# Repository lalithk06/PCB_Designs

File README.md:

# 🖥️ PCB Designs Repository

Welcome to the **PCB Designs** repository!  
This repo contains various **KiCad PCB design projects** for electronics and embedded systems, aimed at learning and experimentation.

---

| 🔗 Project Name         | 📜 Description                                                   | ✅ Status                | 📁 Link |
|:-----------------------:|:---------------------------------------------------------------:|:------------------------|:-------:|
| 🔥 Fire Alarm System    | A light-based fire alarm circuit using an LDR and transistor.   | [x] Schematic <br> [x] PCB | [View Project](./Fire_Alarm/README.md) |
| ⚡ Relay Driver Circuit  | A single-channel relay driver for MCU load control.            | [x] Schematic <br> [x] PCB | [View Project](./Relay_Driver/README.md) |
| 🤖 PID Line Follower PCB | ESP32-based autonomous line follower with custom PCB (power zoning, motor driver, sensors). | [x] Schematic <br> [x] PCB | [View Project](https://github.com/lalithk06/PID-Line-Follower) |
| ⚡ ESP32 Smart Plug | ESP32-S3 based smart plug with mains power control, relay switching, protection, and USB interface. | [x] Schematic <br> [x] PCB | [View Project](https://github.com/lalithk06/ESP32_Smart_Plug) |
| 🌍 ESP32 Indoor Environment Quality Monitor | A 4-layer ESP32-based embedded monitoring system designed for real-time indoor environmental sensing, featuring multi-sensor I2C integration, clean power architecture, OLED interface, data logging, and battery/USB-powered operation. | [x] Schematic <br> [x] PCB | [View Project](./ESP32_IEQ_Monitor) |
| 🔌 USB-C PD Power Supply | A USB Type-C Power Delivery trigger board based on the CH224A, supporting selectable 5V/9V/12V/20V/28V outputs via DIP switches or I²C, with onboard buck conversion, input protection, voltage indication, and screw terminal output. | [x] Schematic <br> [] PCB | [View Project](./USB-C_Power_Supply) |

---

## 🛠 Tools & Workflow
- **KiCad v9.x**   → Schematic & PCB design  
- **Git & GitHub** → Version control and collaboration  
- **Markdown**     → Project documentation

---

## 🚀 How to Use
Clone the repository:
   ```bash
   git clone https://github.com/<your-username>/PCB_Designs.git

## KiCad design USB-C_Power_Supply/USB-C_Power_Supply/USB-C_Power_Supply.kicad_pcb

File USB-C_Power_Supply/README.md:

# USB-C Power Supply (5V / 9V / 12V / 20V / 28V)

A compact USB Type-C Power Delivery (USB-PD) trigger board capable of requesting fixed PDO voltages from a USB-C PD charger and providing a regulated **3.3V rail** for onboard logic. The board is based on the **CH224A USB PD Sink Controller** and supports both **DIP-switch voltage selection** and **I²C control**.

---

## Features

- USB Type-C Power Delivery Sink
- Selectable Output Voltages
  - 5V
  - 9V
  - 12V
  - 20V
  - 28V (USB PD 3.1 EPR)
- CH224A USB PD Sink Controller
- MCP16331 Buck Converter (5V–28V → 3.3V)
- TVS Surge Protection
- PMOS Reverse Polarity Protection
- USB Data Line ESD Protection
- Output Voltage Indicator LEDs
- Power Good / Error Indicator
- I²C Interface
- Screw Terminal Output
- Mounting Holes

---

# Board Overview

---

# Project Images

## Schematic

---

## PCB Layout

### Top Layer

### Bottom Layer

---

## 3D Model

### Top View

### Bottom View

---

# Hardware Architecture

## USB-C Input

The board receives power from a USB Type-C PD compliant charger.

### Components

- USB Type-C Receptacle
- TVS Protection
- PMOS Reverse Polarity Protection
- USBLC6 ESD Protection
- CH224A PD Controller

The USB connector provides:

- VBUS
- CC1
- CC2
- D+
- D-

---

## USB Power Delivery Controller

The CH224A negotiates the requested voltage with the USB PD source.

Unlike traditional USB-C sink implementations, **no external 5.1kΩ Rd resistors are required** because the CH224A integrates the complete USB sink detection circuitry internally.

---

# Voltage Selection

The requested PDO is selected using the CFG pins.

## DIP Switch Mode

Three DIP switches control:

- CFG1
- CFG2
- CFG3

| Output Voltage | CFG1 | CFG2 | CFG3 |
|---------------|------|------|------|
| 5V | X | X | X |
| 9V | 0 | 0 | 0 |
| 12V | 0 | 0 | 1 |
| 20V | 0 | 1 | 1 |
| 28V | 0 | 1 | 0 |

Where

- X = Don't Care
- 0 = GND
- 1 = Pull-up

---

# I²C Mode

The CH224A also supports I²C control.

The I²C connector exposes:

- SDA
- SCL
- GND

This allows an external MCU to dynamically request different PDO voltages without changing the DIP switches.

---

# Output

The negotiated USB PD voltage is available at:

- Screw Terminal Connector

Supported outputs

- 5V
- 9V
- 12V
- 20V
- 28V

> **Output current depends entirely on the connected USB PD adapter and USB-C cable.**

---

# 3.3V Power Supply

The onboard electronics operate from a dedicated 3.3V rail.

Power conversion:

```
    5V–28V
      │
      ▼
   MCP16331
Buck Converter
      │
      ▼
  3.3V Rail
```

The buck converter powers:

- CH224A
- MC14051
- Indicator LEDs
- I²C Interface

---

# Output Voltage Indicators

Five LEDs indicate the negotiated USB PD voltage.

| LED | Voltage |
|------|---------|
| LED1 | 5V |
| LED2 | 9V |
| LED3 | 12V |
| LED4 | 20V |
| LED5 | 28V |

Only one LED is illuminated at a time.

---

# Error Indicator

The CH224A provides a **Power Good (PG)** output.

The PG output is **Active Low**.

## Normal Operation

```
PG = LOW
```

The NMOS remains OFF.

The Error LED remains OFF.

---

## Error Condition

```
PG = HIGH
```

The NMOS turns ON.

The Error LED turns ON.

Possible causes include:

- USB PD negotiation failure
- Unsupported PDO request
- Charger removed
- Fault condition

---

# Protection Features

## TVS Protection

A TVS diode protects the VBUS line against:

- ESD
- Cable transients
- Voltage spikes

The TVS is placed immediately after the USB-C connector.

---

## Reverse Polarity Protection

A PMOS transistor provides reverse polarity protection.

Advantages

- Very low voltage drop
- Automatic recovery
- No fuse replacement required

---

## CC Line Protection

22Ω series resistors improve robustness against:

- ESD
- Ringing
- Cable transients

---

# eMarker Simulation Mode

USB PD 3.1 requires an electronically marked cable for voltages greater than 20V or powers exceeding 60W.

The CH224A provides an **eMarker Simulation Mode**.

To enable:

Connect

```
1kΩ

CC2 → GND
```

This allows requesting

- 28V PDO

using a standard USB-C connector.

Refer to the CH224A datasheet for further details.

---

# Applications

- USB PD Bench Supply
- Embedded Development
- Rapid Prototyping
- Battery Charging
- Robotics
- Industrial Electronics
- Portable Instruments
- USB PD Testing
- IoT Projects

---

# Operating Procedure

## DIP Switch Mode

1. Connect a USB PD charger.
2. Configure the DIP switches for the desired voltage.
3. Apply power.
4. The CH224A negotiates the selected PDO.
5. Verify the output voltage using the indicator LED.
6. Use the output at J2.

---

## I²C Mode

1. Connect an external MCU.
2. Initialize the CH224A over I²C.
3. Send the desired PDO request.
4. Wait for negotiation to complete.
5. Monitor the PG signal.
6. Use the negotiated output voltage.

---

# Notes

- The output voltage is available only when connected to a USB PD compliant source.
- 28V operation requires a USB PD 3.1 EPR compatible adapter.
- Maximum available current depends on the USB PD source and cable capability.
- Use high-quality USB-C cables for high-power operation.
- The board does not generate voltages internally; it only negotiates and passes through supported USB PD voltages.

---

# Specifications

| Parameter | Value |
|-----------|-------|
| Input Connector | USB Type-C |
| USB PD Version | USB PD 3.1 |
| Supported PDOs | 5V, 9V, 12V, 20V, 28V |
| Controller | CH224A |
| Logic Supply | 3.3V |
| Buck Converter | MCP16331 |
| Voltage Selection | DIP Switch / I²C |
| Output Connector | Screw Terminal |
| Reverse Polarity Protection | PMOS |
| Surge Protection | TVS |
| USB ESD Protection | USBLC6 |
| Mounting | 4 × Mounting Holes |

---

# License

This hardware design is released under the MIT License unless stated otherwise.

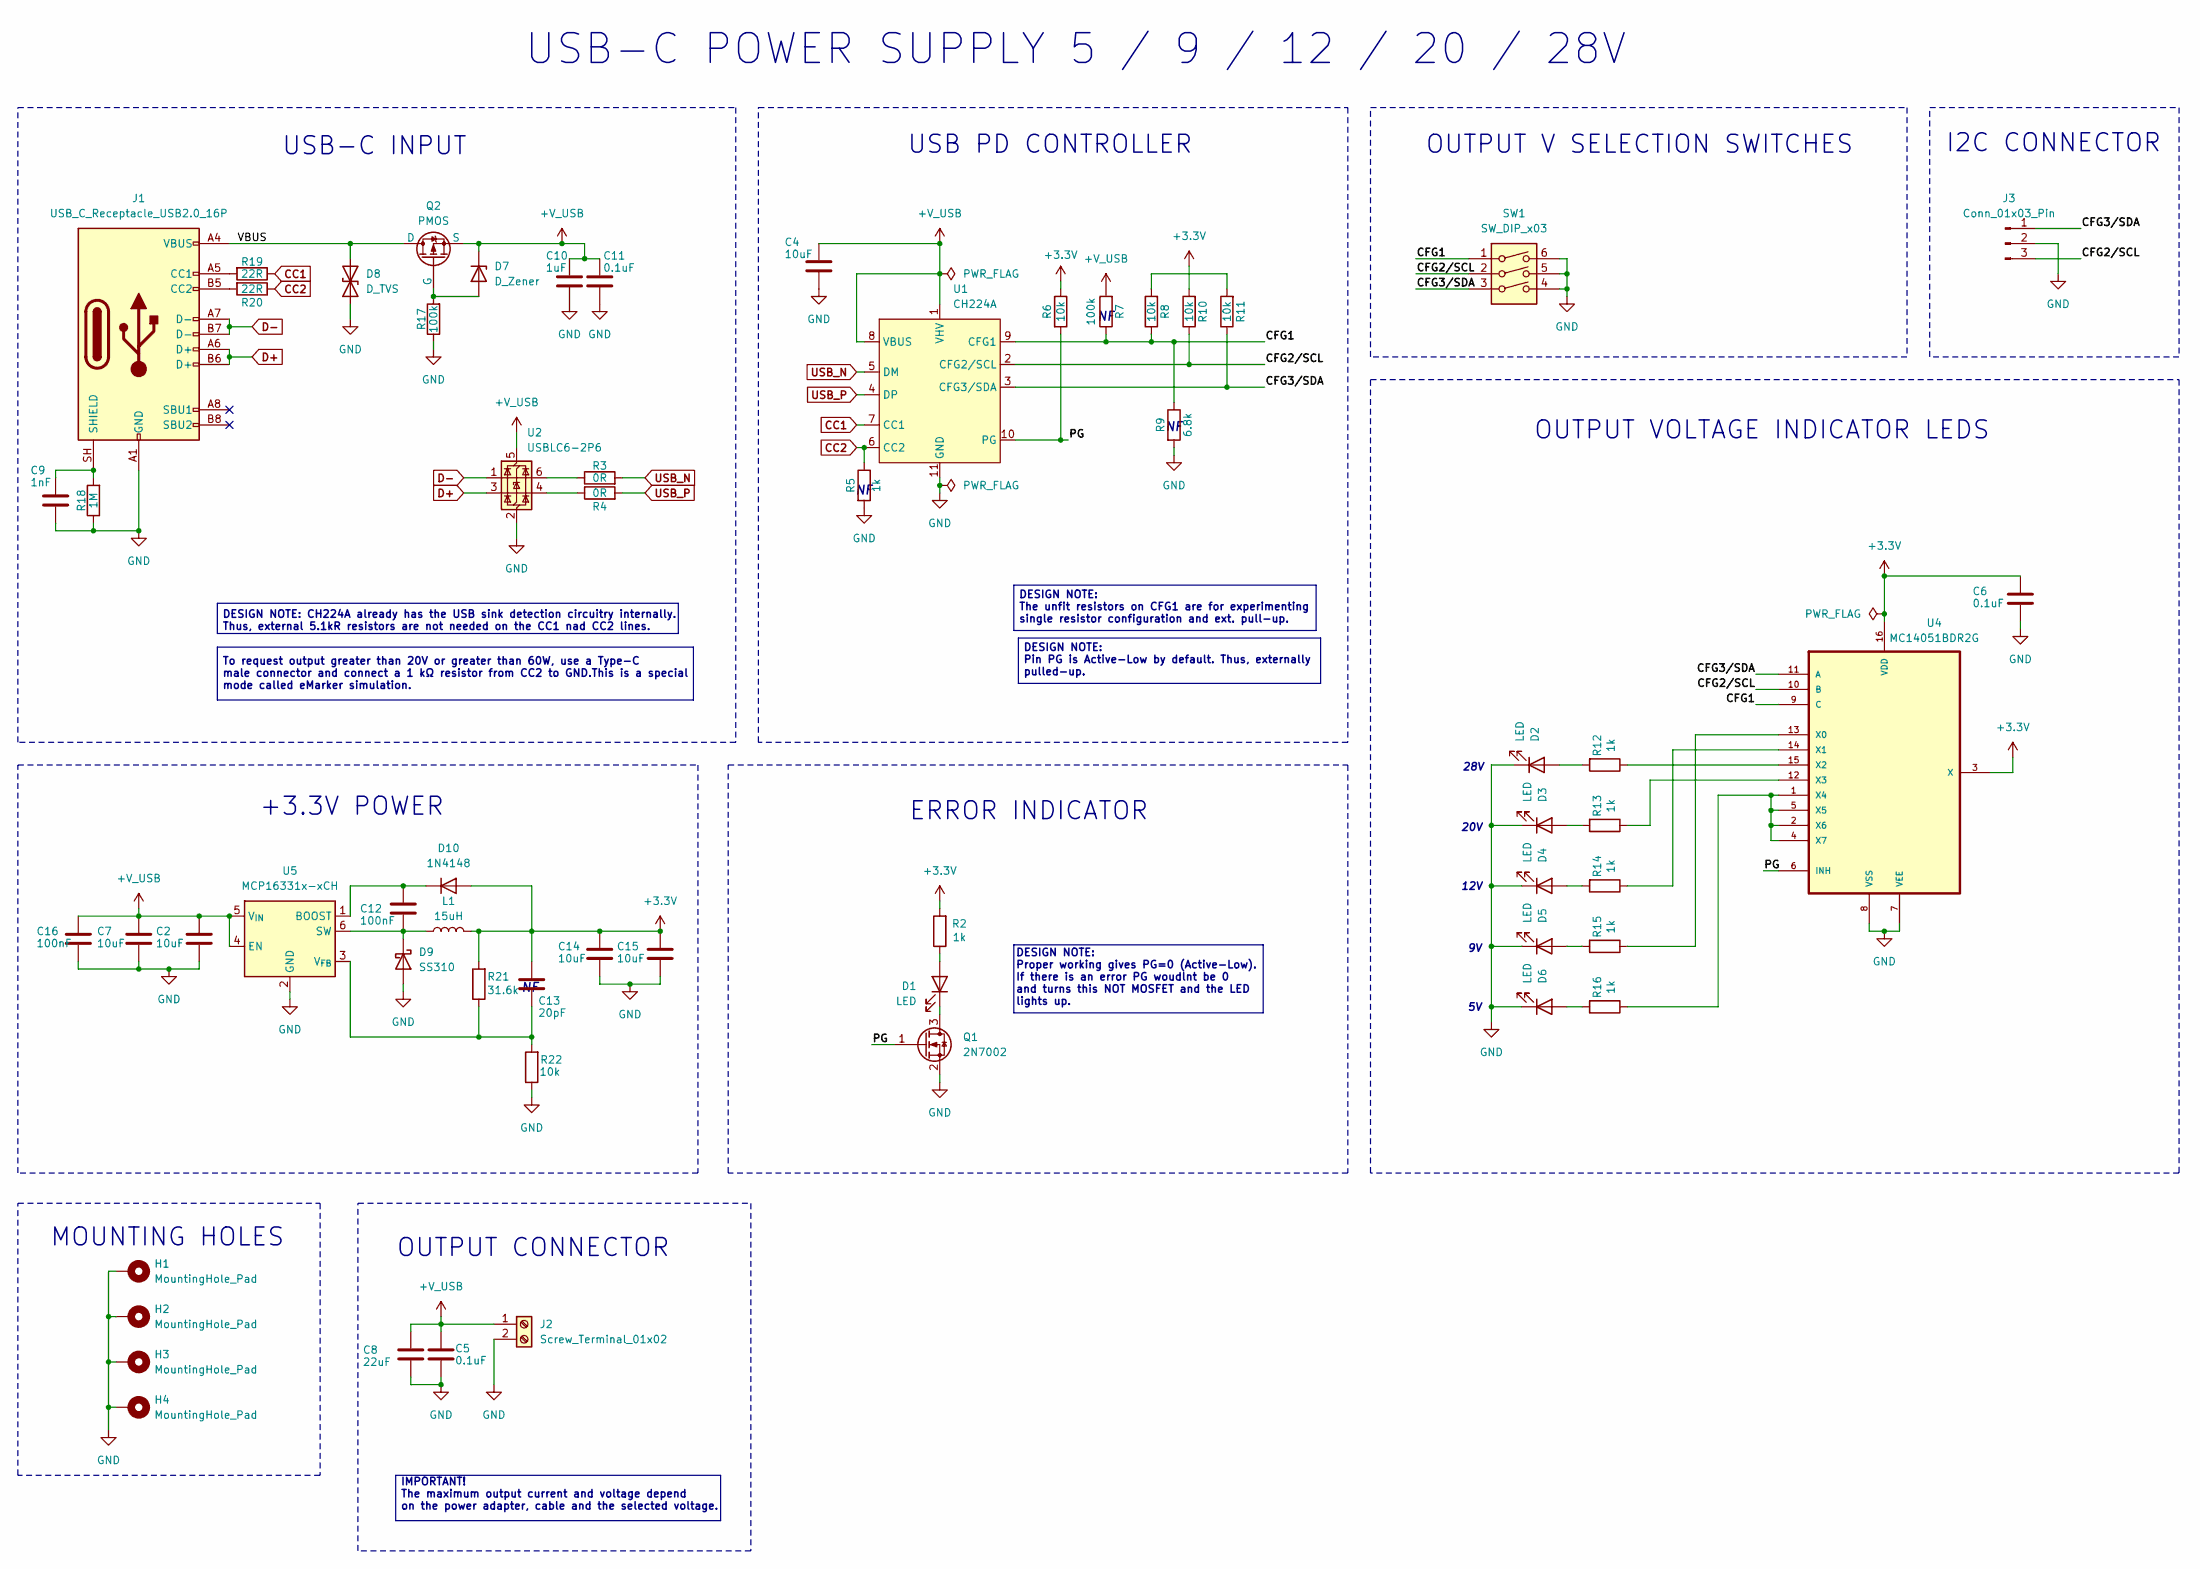
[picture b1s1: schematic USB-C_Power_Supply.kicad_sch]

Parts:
C2, C4, C7, C14, C15: 10uF; C_1206_3216Metric
C5, C6, C11: 0.1uF; C_0603_1608Metric
C8: 22uF; C_1210_3225Metric
C9: 1nF; C_0603_1608Metric
C10: 1uF; C_0805_2012Metric
C12, C16: 100nF; C_0603_1608Metric
C13: 20pF; C_0603_1608Metric
D1, D2, D3, D4, D5, D6: LED; LED_0603_1608Metric
D7: D_Zener; D_SOD-123
D8: D_TVS; D_SMB
D9: SS310; D_SMA
D10: 1N4148; D_DO-35_SOD27_P7.62mm_Horizontal
H1, H2, H3, H4: MountingHole_Pad; MountingHole_2.5mm_Pad
J1: USB_C_Receptacle_USB2.0_16P; USB_C_Receptacle_GCT_USB4105-xx-A_16P_TopMnt_Horizontal
J2: Screw_Terminal_01x02; CUI_TB007-508-02BE
J3: Conn_01x03_Pin; PinHeader_1x03_P2.54mm_Vertical
L1: 15uH; L_6.3x6.3_H3
Q1: 2N7002; SOT-23
Q2: PMOS; SOT-23
R2, R5, R12, R13, R14, R15, R16: 1k; R_0603_1608Metric
R3, R4: 0R; R_0603_1608Metric
R6, R8, R10, R11, R22: 10k; R_0603_1608Metric
R7, R17: 100k; R_0603_1608Metric
R9: 6.8k; R_0603_1608Metric
R18: 1M; R_0603_1608Metric
R19, R20: 22R; R_0603_1608Metric
R21: 31.6k; R_0603_1608Metric
SW1: SW_DIP_x03; SW_DIP_SPSTx03_Slide_6.7x9.18mm_W8.61mm_P2.54mm_LowProfile
U1: CH224A
U2: USBLC6-2P6; SOT-666
U4: MC14051BDR2G
U5: MCP16331x-xCH; SOT-23-6

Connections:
+3.3V: C6.1, C13.1, C14.1, C15.1, D10.2 (A), L1.2, R2.2, R6.1, R10.2, R21.2, U4.3 (X), U4.16 (VDD)
+V_USB: C2.1, C4.1, C5.1, C7.1, C8.1, C10.1, C11.1, C16.1, D7.1 (K), J2.1, Q2.3 (S), R7.2, U1.1 (VHV), U1.8 (VBUS), U2.5 (VBUS), U5.4 (EN), U5.5 (V_{IN})
/CFG1: R7.1, R8.1, R9.1, SW1.1, U1.9 (CFG1), U4.9 (C)
/CFG2/SCL: J3.3, R10.1, SW1.2, U1.2 (CFG2/SCL), U4.10 (B)
/CFG3/SDA: J3.1, R11.1, SW1.3, U1.3 (CFG3/SDA), U4.11 (A)
/PG: Q1.1 (G), R6.2, U1.10 (PG), U4.6 (INH)
CC1: R19.1, U1.7 (CC1)
CC2: R5.1, R20.1, U1.6 (CC2)
D+: J1.A6 (D+), J1.B6 (D+), U2.3 (I/O2)
D-: J1.A7 (D-), J1.B7 (D-), U2.1 (I/O1)
GND: C2.2, C4.2, C5.2, C6.2, C7.2, C8.2, C9.2, C10.2, C11.2, C14.2, C15.2, C16.2, D2.1 (K), D3.1 (K), D4.1 (K), D5.1 (K), D6.1 (K), D8.1 (A1), D9.2 (A), H1.1 (1_1), H2.1 (1_1), H3.1 (1_1), H4.1 (1_1), J1.A1 (GND), J1.A12 (GND), J1.B1 (GND), J1.B12 (GND), J2.2, J3.2, Q1.2 (S), R5.2, R9.2, R17.1, R18.1, R22.1, SW1.4, SW1.5, SW1.6, U1.11 (GND), U2.2 (GND), U4.7 (VEE), U4.8 (VSS), U5.2 (GND)
unnamed: D1.2 (A), R2.1
unnamed: D1.1 (K), Q1.3 (D)
unnamed: D2.2 (A), R12.2
unnamed: D3.2 (A), R13.2
unnamed: D4.2 (A), R14.2
unnamed: D5.2 (A), R15.2
unnamed: D6.2 (A), R16.2
unnamed: D7.2 (A), Q2.2 (G), R17.2
unnamed: D8.2 (A2), J1.A4 (VBUS), J1.A9 (VBUS), J1.B4 (VBUS), J1.B9 (VBUS), Q2.1 (D)
unnamed: C12.2, D9.1 (K), L1.1, U5.6 (SW)
unnamed: C12.1, D10.1 (K), U5.1 (BOOST)
unnamed: J1.A5 (CC1), R19.2
unnamed: J1.B5 (CC2), R20.2
unnamed: C9.1, J1.SH (SHIELD), R18.2
unnamed: R3.1, U2.6 (I/O1)
unnamed: R4.1, U2.4 (I/O2)
unnamed: R8.2, R11.2
unnamed: R15.1, U4.13 (X0)
unnamed: R14.1, U4.14 (X1)
unnamed: R12.1, U4.15 (X2)
unnamed: R13.1, U4.12 (X3)
unnamed: R16.1, U4.1 (X4), U4.2 (X6), U4.4 (X7), U4.5 (X5)
unnamed: C13.2, R21.1, R22.2, U5.3 (V_{FB})
USB_N: R3.2, U1.5 (DM)
USB_P: R4.2, U1.4 (DP)

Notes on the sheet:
ERROR INDICATOR
OUTPUT V SELECTION SWITCHES
DESIGN NOTE: The unfit resistors on CFG1 are for experimenting single resistor configuration and ext. pull-up.
DESIGN NOTE: Pin PG is Active-Low by default. Thus, externally pulled-up.
+3.3V POWER
USB-C INPUT
USB PD CONTROLLER
I2C CONNECTOR
DESIGN NOTE: Proper working gives PG=0 (Active-Low). If there is an error PG woudlnt be 0 and turns this NOT MOSFET and the LED lights up.
DESIGN NOTE: CH224A already has the USB sink detection circuitry internally. Thus, external 5.1kR resistors are not needed on the CC1 nad CC2 lines.
OUTPUT VOLTAGE INDICATOR LEDS
20V
OUTPUT CONNECTOR
IMPORTANT! The maximum output current and voltage depend on the power adapter, cable and the selected voltage.
To request output greater than 20V or greater than 60W, use a Type-C male connector and connect a 1 kΩ resistor from CC2 to GND.This is a special mode called eMarker simulation.
28V
MOUNTING HOLES
USB-C POWER SUPPLY 5 / 9 / 12 / 20 / 28V
12V

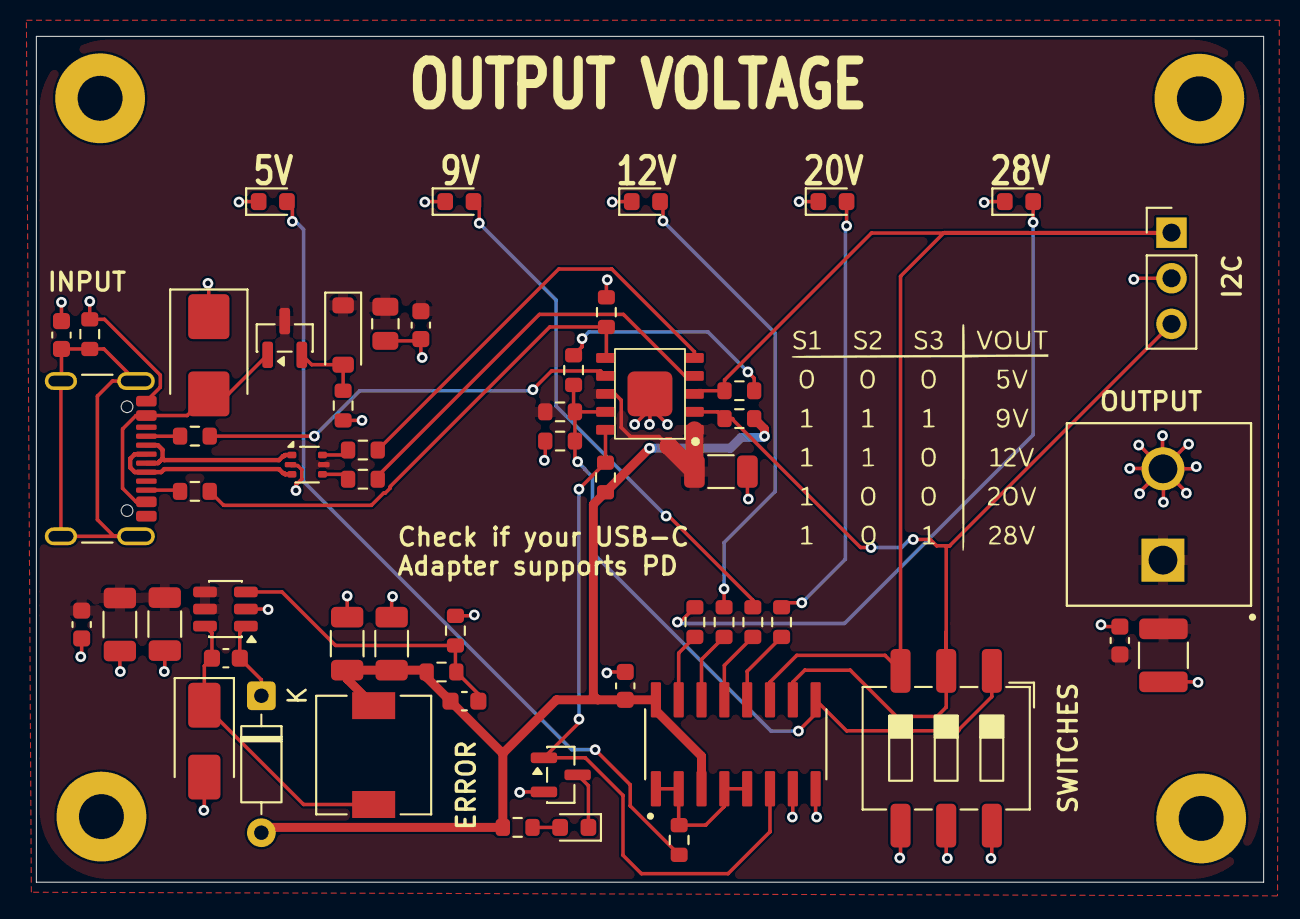
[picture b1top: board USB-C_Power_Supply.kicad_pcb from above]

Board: 2 copper layers, 68.3 x 47.1 mm, 60 parts (0 on the bottom side), 36 nets.

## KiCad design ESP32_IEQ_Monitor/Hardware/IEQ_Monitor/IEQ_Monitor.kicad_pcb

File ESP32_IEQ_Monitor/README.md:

# 🌿 ESP32 Indoor Environmental Quality (IEQ) Monitor — Hardware Design  
<p align="center">
  A compact multi-sensor environmental monitoring system built using ESP32
</p>

---

This project showcases the schematic and PCB design of a **multi-sensor Indoor Environmental Quality (IEQ) monitoring system**, capable of measuring air quality, CO₂ levels, temperature, humidity, and ambient light.

It focuses on **real-world embedded hardware design**, emphasizing **power integrity, sensor interfacing, and clean PCB layout practices**.

---

## ⚙️ Working Principle

- ESP32 acts as the main controller (Wi-Fi + BLE)
- Sensors connected via I2C:
  - BME280 → Temperature, Humidity, Pressure  
  - SCD40 → CO₂ concentration  
  - ENS160 → Air quality (VOC, AQI)  
  - OPT3001 → Ambient light  
- Data is:
  - Displayed on OLED
  - Logged to microSD card
- RTC provides timestamps
- Buttons + LEDs + buzzer for interaction

---

## 🎯 Objective

To design a robust hardware platform demonstrating:

- Multi-sensor integration  
- Clean power architecture  
- I2C-based expansion  
- Practical PCB layout techniques  
- Embedded system design  

---

## 🧩 Hardware Overview

| No. | Component | Role |
|------|------------|--------|
| 1 | ESP32 | Main MCU |
| 2 | BME280 | Temp, Humidity, Pressure |
| 3 | SCD40 | CO₂ sensor |
| 4 | ENS160 | Air quality |
| 5 | OPT3001 | Light sensor |
| 6 | RTC | Timekeeping |
| 7 | OLED | Display |
| 8 | microSD | Data logging |
| 9 | MP1584 | Buck converter |
| 10 | AP2112K | LDO regulator |
| 11 | Buttons/LEDs | User interface |

---

## 🔋 Power Architecture

### USB Power Path

- Reverse protection  
- Clean regulated output  

---

### Battery Power Path

- High efficiency  
- Standalone operation  

---

### Design Considerations

- No reverse current into LDO  
- Unified 3V3 rail  
- Proper decoupling (10µF + 0.1µF)  
- Stable supply for ESP32  

---

## 🧠 PCB Design Details

### Stackup (4 Layers)

| Layer | Function |
|------|--------|
| L1 | Components + signals |
| L2 | GND plane |
| L3 | 3V3 plane |
| L4 | Routing |

---

### Grounding

- Solid ground plane  
- Via stitching  
- Low impedance return paths  

---

### Routing Strategy

- Power routed first  
- Signals routed next  
- Ground poured last  

---

## 📷 Preview

### Schematic  

### PCB  

### 3D View  

---

## ✨ Key Features

- Multi-sensor monitoring  
- Dual power input  
- 4-layer PCB  
- Clean grounding  
- Expandable I2C  
- Data logging  
- OLED interface  

---

## 🧪 Design Challenges

- Power backflow handling  
- Net naming (3V3 vs ESP32_3V3)  
- Clearance & DRC issues  
- Ground plane interference  

---

## 🚀 Future Improvements

- Voice assistant integration  
- Mobile app  
- OTA updates  
- Battery management  
- Enclosure design  

---

## 📚 Learning Outcomes

- Power design
- Multilayer PCB Designing
- Types of Vias
- Via Stitching
- PCB routing techniques
- Grounding strategies  
- Sensor interfacing  
- Debugging hardware  

---

## 🤝 Contributions

Open for improvements and suggestions.

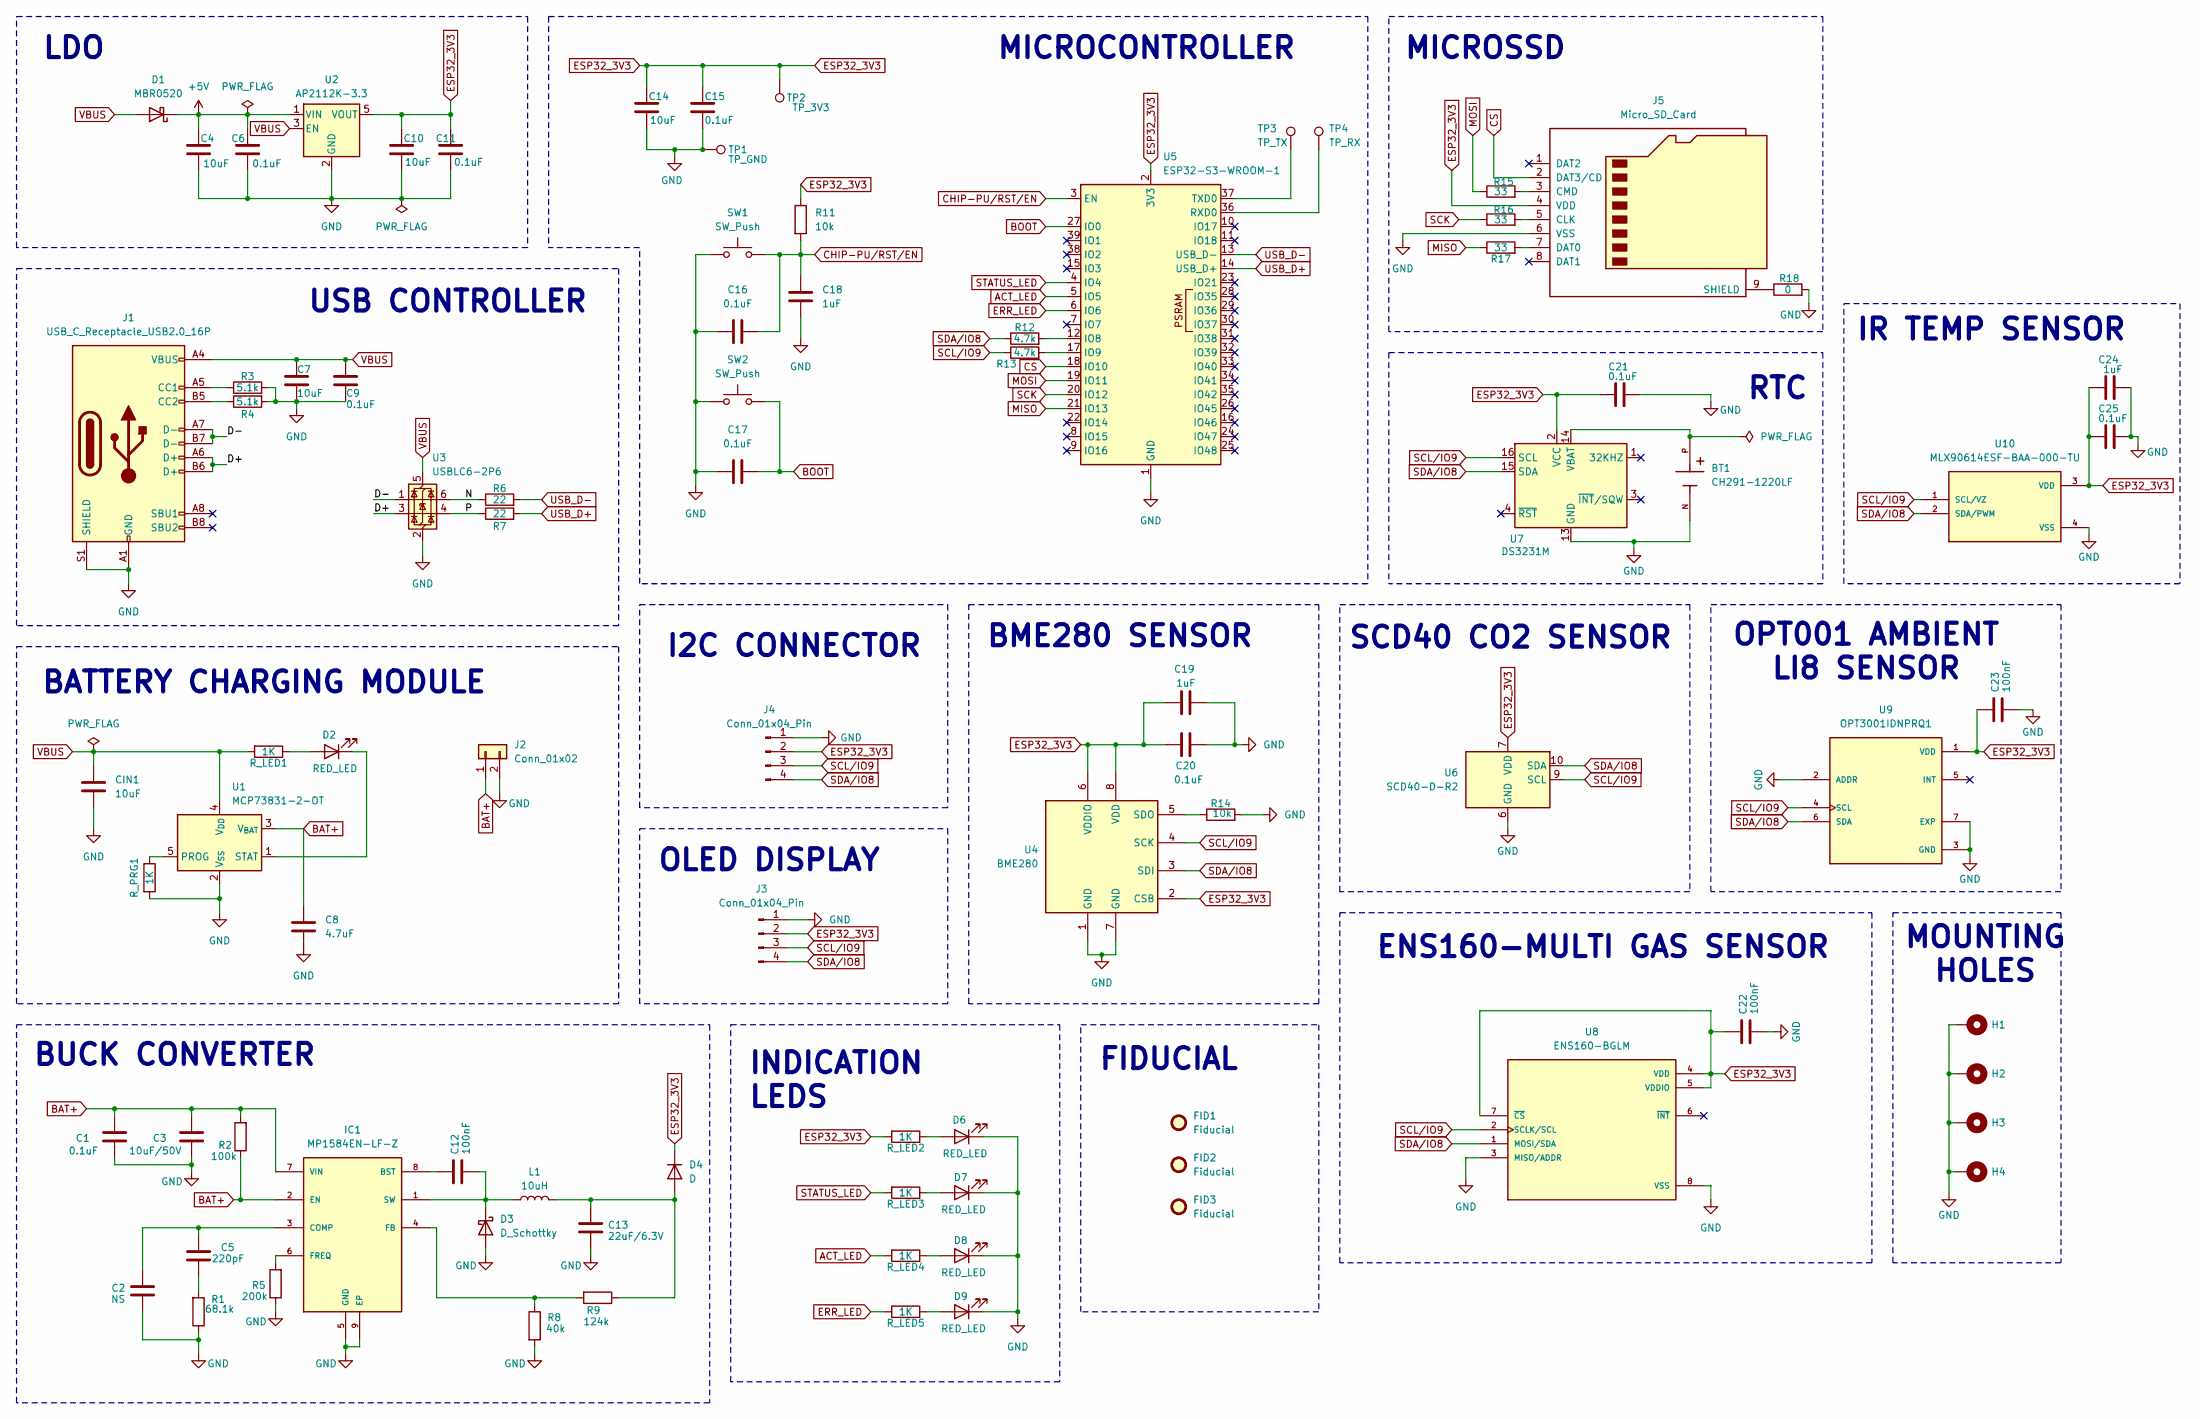
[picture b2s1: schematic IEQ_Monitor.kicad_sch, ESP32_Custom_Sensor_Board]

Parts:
BT1: CH291-1220LF; BAT_CH291-1220LF; PARTREV A
C1: 0.1uF; C_0805_2012Metric
C2: NS; C_0805_2012Metric
C3: 10uF/50V; C_0805_2012Metric
C4, C7, C10, C14: 10uF; C_0805_2012Metric
C5: 220pF; C_0805_2012Metric
C6, C9, C11, C15, C16, C17, C20, C21, C25: 0.1uF; C_0603_1608Metric
C8: 4.7uF; C_0805_2012Metric
C12, C22, C23: 100nF; C_0805_2012Metric
C13: 22uF/6.3V; C_0805_2012Metric
C18, C19, C24: 1uF; C_0603_1608Metric
CIN1: 10uF; C_0805_2012Metric
D1: MBR0520; D_SOD-123
D2, D6, D7, D8, D9: RED_LED; LED_0201_0603Metric
D3: D_Schottky; D_SMA
D4: D; D_SOD-123F
FID1, FID2, FID3: Fiducial; Fiducial_0.75mm_Mask1.5mm
H1, H2, H3, H4: MountingHole_Pad; MountingHole_2.2mm_M2_Pad_Via
IC1: MP1584EN-LF-Z; SOIC127P600X170-9N; MOUSER_PART_NUMBER 946-MP1584ENLFZ
J1: USB_C_Receptacle_USB2.0_16P; USB_C_Receptacle_HCTL_HC-TYPE-C-16P-01A
J2: Conn_01x02; JST_PH_S2B-PH-K_1x02_P2.00mm_Horizontal
J3, J4: Conn_01x04_Pin; PinHeader_1x04_P2.54mm_Vertical
J5: Micro_SD_Card; microSD_HC_Hirose_DM3AT-SF-PEJM5
L1: 10uH; L_6.3x6.3_H3
R1: 68.1k; R_0603_1608Metric
R2: 100k; R_0603_1608Metric
R3, R4: 5.1k; R_0603_1608Metric
R5: 200k; R_0603_1608Metric
R6, R7: 22; R_0603_1608Metric
R8: 40k; R_0603_1608Metric
R9: 124k; R_0603_1608Metric
R11, R14: 10k; R_0603_1608Metric
R12, R13: 4.7k; R_0603_1608Metric
R15, R16, R17: 33; R_0603_1608Metric
R18: 0; R_0603_1608Metric
R_LED1, R_LED2, R_LED3, R_LED4, R_LED5: 1K; R_0603_1608Metric
R_PRG1: 1K; R_0603_1608Metric
SW1, SW2: SW_Push; SW_Push_SPST_NO_Alps_SKRK
TP1: TP_GND; TestPoint_Pad_D2.5mm
TP2: TP_3V3; TestPoint_Pad_D2.5mm
TP3: TP_TX; TestPoint_Pad_D2.5mm
TP4: TP_RX; TestPoint_Pad_D2.5mm
U1: MCP73831-2-OT; SOT-23-5
U2: AP2112K-3.3; SOT-23-5
U3: USBLC6-2P6; SOT-666
U4: BME280; Bosch_LGA-8_2.5x2.5mm_P0.65mm_ClockwisePinNumbering
U5: ESP32-S3-WROOM-1
U6: SCD40-D-R2; Sensirion_SCD4x-1EP_10.1x10.1mm_P1.25mm_EP4.8x4.8mm
U7: DS3231M; SOIC-16W_7.5x10.3mm_P1.27mm
U8: ENS160-BGLM; XDCR_ENS160-BGLM; PARTREV 1.3
U9: OPT3001IDNPRQ1; SON65P200X200X65-7N; PARTREV 01/2018
U10: MLX90614ESF-BAA-000-TU; TO254P942H425-4; PARTREV 13

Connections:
+5V: C4.1, C6.1, D1.1 (K), U2.1 (VIN)
/D+: J1.A6 (D+), J1.B6 (D+), U3.3 (I/O2)
/D-: J1.A7 (D-), J1.B7 (D-), U3.1 (I/O1)
/N: R6.1, U3.6 (I/O1)
/P: R7.1, U3.4 (I/O2)
ACT_LED: R_LED4.2, U5.5 (IO5)
BAT+: C1.1, C3.1, C8.1, IC1.2 (EN), IC1.7 (VIN), J2.1, R2.1, R2.2, U1.3 (V_{BAT})
BOOT: C17.2, SW2.2, U5.27 (IO0)
CHIP-PU/RST/EN: C16.2, C18.1, R11.2, SW1.2, U5.3 (EN)
CS: J5.2 (DAT3/CD), U5.18 (IO10)
ERR_LED: R_LED5.2, U5.6 (IO6)
ESP32_3V3: C10.1, C11.1, C14.1, C15.1, C19.1, C20.1, C21.1, C22.1, C23.1, C24.1, C25.1, D4.1 (K), J3.2, J4.2, J5.4 (VDD), R11.1, R_LED2.2, TP2.1 (1_1), U2.5 (VOUT), U4.2 (CSB), U4.6 (VDDIO), U4.8 (VDD), U5.2 (3V3), U6.7 (VDD), U6.19 (VDD), U7.2 (VCC), U8.4 (VDD), U8.5 (VDDIO), U8.7 (~CS), U9.1 (VDD), U10.3 (VDD)
GND: BT1.N, C1.2, C2.2, C3.2, C4.2, C6.2, C7.2, C8.2, C9.2, C10.2, C11.2, C13.2, C14.2, C15.2, C16.1, C17.1, C18.2, C19.2, C20.2, C21.2, C22.2, C23.2, C24.2, C25.2, CIN1.1, D3.2 (A), D6.1 (K), D7.1 (K), D8.1 (K), D9.1 (K), H1.1 (1_1), H2.1 (1_1), H3.1 (1_1), H4.1 (1_1), IC1.5 (GND), IC1.9 (EP), J1.A1 (GND), J1.A12 (GND), J1.B1 (GND), J1.B12 (GND), J1.S1 (SHIELD), J2.2, J3.1, J4.1, J5.6 (VSS), R1.1, R3.2, R4.2, R5.1, R8.2, R14.2, R18.2, R_PRG1.2, SW1.1, SW2.1, TP1.1 (1_1), U1.2 (V_{SS}), U2.2 (GND), U3.2 (GND), U4.1 (GND), U4.7 (GND), U5.1 (GND), U5.40 (GND), U5.41 (GND), U6.6 (GND), U6.20 (GND), U6.21 (GND), U7.5 (GND), U7.6 (GND), U7.7 (GND), U7.8 (GND), U7.9 (GND), U7.10 (GND), U7.11 (GND), U7.12 (GND), U7.13 (GND), U8.3 (MISO/ADDR), U8.8 (VSS), U8.9 (VSS), U9.2 (ADDR)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
MISO: R17.1, U5.21 (IO13)
MOSI: R15.1, U5.19 (IO11)
unnamed: C5.2, R1.2
unnamed: D2.2 (A), R_LED1.1
unnamed: D2.1 (K), U1.1 (STAT)
unnamed: C12.2, D3.1 (K), IC1.1 (SW), L1.1
unnamed: C13.1, D4.2 (A), L1.2, R9.1
unnamed: D6.2 (A), R_LED2.1
unnamed: D7.2 (A), R_LED3.1
unnamed: D8.2 (A), R_LED4.1
unnamed: D9.2 (A), R_LED5.1
unnamed: C12.1, IC1.8 (BST)
unnamed: C2.1, C5.1, IC1.3 (COMP)
unnamed: IC1.4 (FB), R8.1, R9.2
unnamed: IC1.6 (FREQ), R5.2
unnamed: J1.A5 (CC1), R3.1
unnamed: J1.B5 (CC2), R4.1
unnamed: J5.5 (CLK), R16.2
unnamed: J5.3 (CMD), R15.2
unnamed: J5.7 (DAT0), R17.2
unnamed: J5.9 (SHIELD), R18.1
unnamed: R_PRG1.1, U1.5 (PROG)
unnamed: R14.1, U4.5 (SDO)
unnamed: R12.2, U5.12 (IO8)
unnamed: R13.2, U5.17 (IO9)
unnamed: TP4.1 (1_1), U5.36 (RXD0)
unnamed: TP3.1 (1_1), U5.37 (TXD0)
unnamed: BT1.P, U7.14 (VBAT)
SCK: R16.1, U5.20 (IO12)
SCL/IO9: J3.3, J4.3, R13.1, U4.4 (SCK), U6.9 (SCL), U7.16 (SCL), U8.2 (SCLK/SCL), U9.4 (SCL), U10.1 (SCL/VZ)
SDA/IO8: J3.4, J4.4, R12.1, U4.3 (SDI), U6.10 (SDA), U7.15 (SDA), U8.1 (MOSI/SDA), U9.6 (SDA), U10.2 (SDA/PWM)
STATUS_LED: R_LED3.2, U5.4 (IO4)
USB_D+: R7.2, U5.14 (USB_D+)
USB_D-: R6.2, U5.13 (USB_D-)
VBUS: C7.1, C9.1, CIN1.2, D1.2 (A), J1.A4 (VBUS), J1.A9 (VBUS), J1.B4 (VBUS), J1.B9 (VBUS), R_LED1.2, U1.4 (V_{DD}), U2.3 (EN), U3.5 (VBUS)

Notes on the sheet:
RTC
ENS160-MULTI GAS SENSOR
SCD40 CO2 SENSOR
BATTERY CHARGING MODULE
MICROCONTROLLER
OLED DISPLAY
MOUNTING HOLES
MICROSSD
IR TEMP SENSOR
USB CONTROLLER
INDICATION LEDS
I2C CONNECTOR
BME280 SENSOR
FIDUCIAL
OPT001 AMBIENT LI8 SENSOR
BUCK CONVERTER
LDO

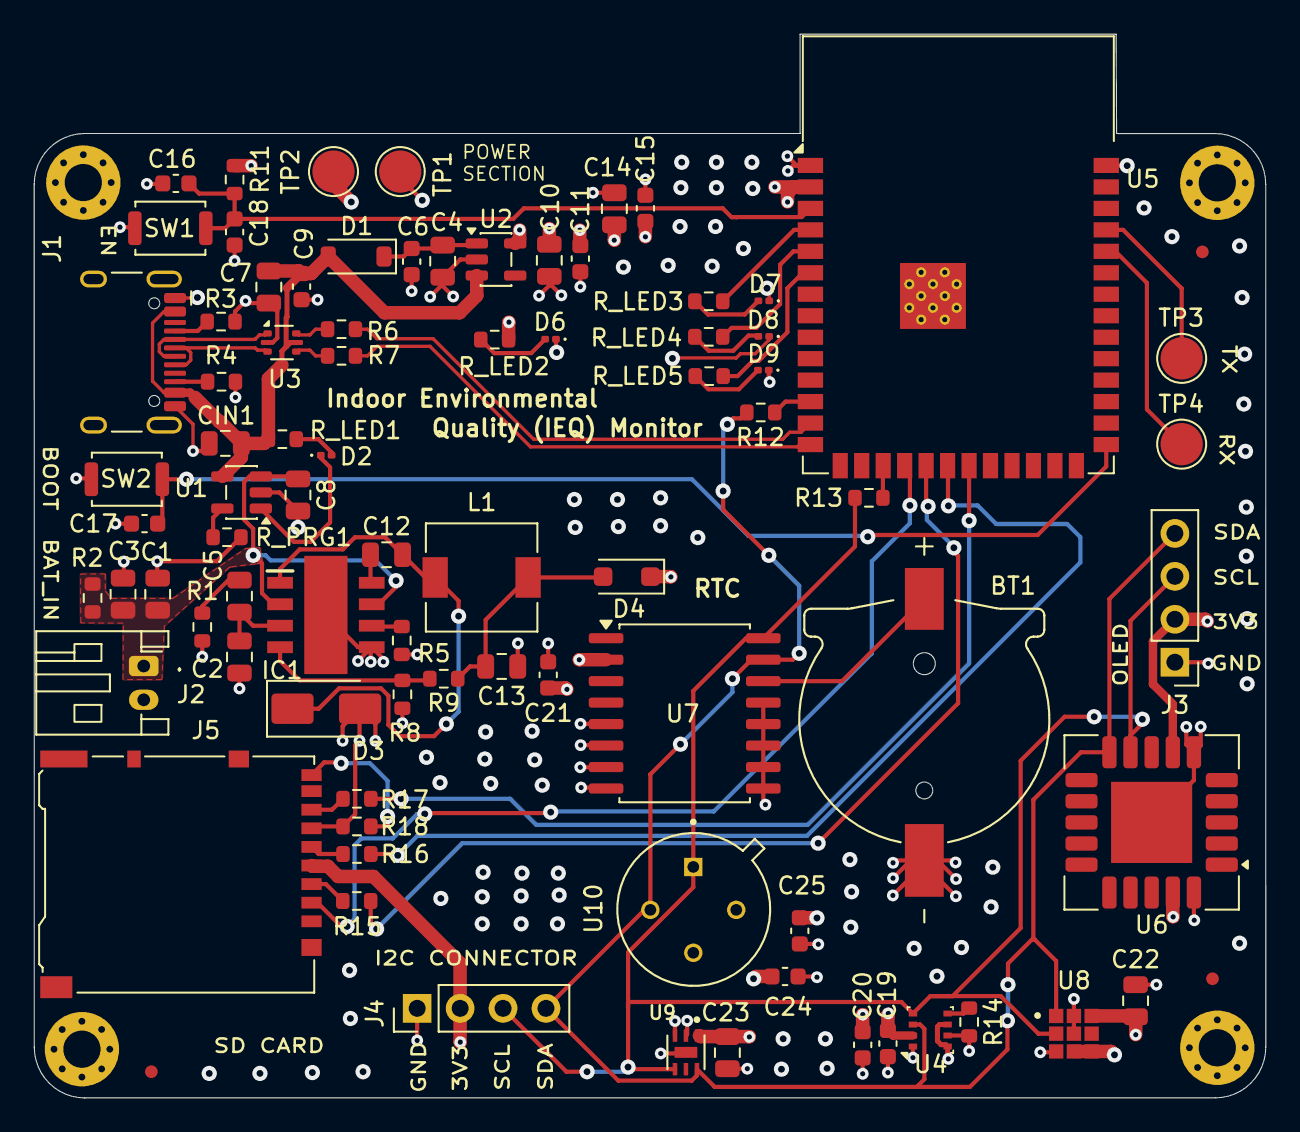
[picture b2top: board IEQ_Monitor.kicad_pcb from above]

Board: 4 copper layers, 72.9 x 62.9 mm, 88 parts (0 on the bottom side), 48 nets.

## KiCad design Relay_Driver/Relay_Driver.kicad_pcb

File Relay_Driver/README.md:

#  🖥 Relay Driver PCB (Single Channel)
  A compact and reliable single-channel relay driver circuit designed in KiCad, suitable for MCU-based automation projects. 

---

##  📌 Overview
  This PCB allows an MCU (like Arduino, ESP32, or Raspberry Pi) to control high-voltage or high-current loads using an electromagnetic relay.

It integrates:

   * MCU-compatible input (logic level control)

   * Flyback diode protection

   * LED status indicator

   * Screw terminals for easy load connection

---

##  🔄 Working
### 1️⃣ Idle State (MCU LOW):

  -The MCU output pin is LOW.

  -The transistor (BC547) remains OFF, preventing current flow through the relay coil.

  -The relay is de-energized, and the COM terminal is connected to NC by default.

  -The LED indicator is OFF.

### 2️⃣ Active State (MCU HIGH):

  -The MCU output pin goes HIGH (logic signal sent).

  -The base resistor (R1) limits current to the transistor base, turning it ON (saturation mode).

  -The transistor conducts, energizing the relay coil.

  -The relay switches from NC to NO, connecting the load between COM and NO.

  -The LED lights up, indicating relay activation.

### 3️⃣ Flyback Diode Protection:

  -When the MCU signal turns OFF, the coil de-energizes, creating a voltage spike.

  -The flyback diode (1N4007) safely dissipates this energy, protecting the transistor and MCU.

---

##  🔧 Features

✅ Supports **5V or 12V relays** (SANYOU SRD series)

✅ **Transistor driver stage (BC547)** for MCU signal amplification

✅ **Flyback diode (1N4007)** for relay coil protection

✅ **LED indicator** for relay ON/OFF status

✅ **Screw terminal output** for load switching (COM, NO, NC)

✅ Compact **single-layer PCB** (ideal for hobby or educational use)

---

##  🔌 Connections
###  Power Header (J1)
  Pin 1: VCC (5V or 12V depending on relay)
  Pin 2: GND

###  MCU Input Header (J2)
  Pin 1: MCU_IN (GPIO from MCU)
  Pin 2: GND (common reference with MCU)

###  Relay Output Header (J3)
  Pin 1: COM (Common terminal)
  Pin 2: NC (Normally Closed)
  Pin 3: NO (Normally Open)

---

## 🖼 PCB Design & Screenshots

### 🔧 Schematic:

### 🔌 PCB Layout:
**Top View:**  

### 🎨 3D Render:

---

##  ⚙ Specifications

  * **Relay Type:** SANYOU SRD (5V or 12V)

  * **Control Voltage:** MCU-compatible (3.3V or 5V logic)

  * **Load Voltage:** Supports AC (up to relay rating) or DC loads

  * **Transistor:** BC547 (NPN driver)

  * **Flyback Diode:** 1N4007 (across coil)

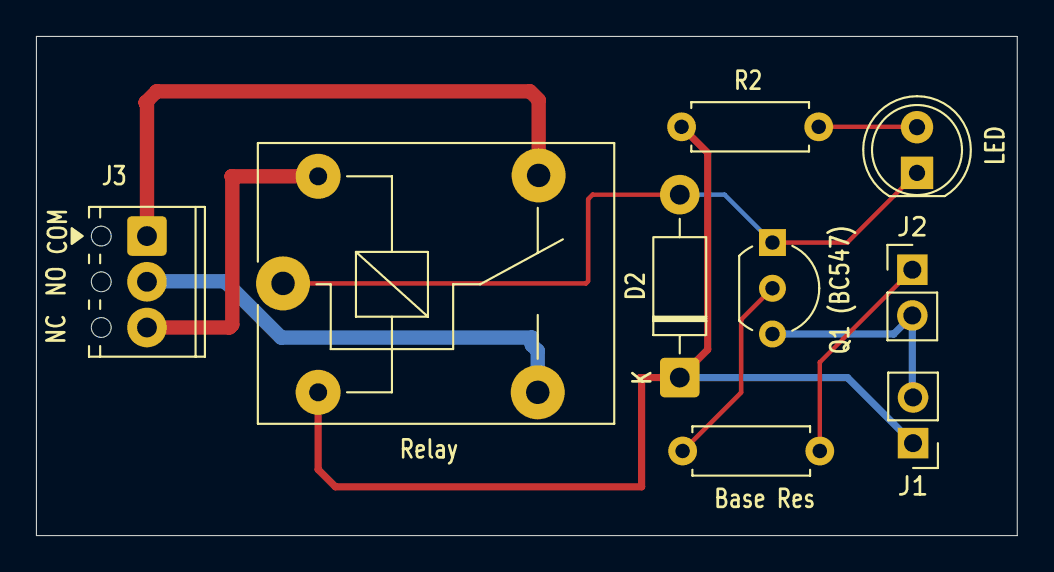
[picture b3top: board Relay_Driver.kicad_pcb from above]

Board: 2 copper layers, 54.5 x 27.7 mm, 9 parts (0 on the bottom side), 9 nets.

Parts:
Base Res: 1k; R_Axial_DIN0207_L6.3mm_D2.5mm_P7.62mm_Horizontal
D2: 1N4007; D_DO-41_SOD81_P10.16mm_Horizontal
J1: Power_IN; PinHeader_1x02_P2.54mm_Vertical
J2: MCU_IN; PinHeader_1x02_P2.54mm_Vertical
J3: Relay_OUT; TerminalBlock_Phoenix_MPT-0,5-3-2.54_1x03_P2.54mm_Horizontal
LED: LED; LED_D5.0mm
Q1 (BC547): BC547; TO-92_Inline_Wide
R2: 330 or 1k; R_Axial_DIN0207_L6.3mm_D2.5mm_P7.62mm_Horizontal
Relay: SANYOU_SRD_Form_C; Relay_SPDT_SANYOU_SRD_Series_Form_C

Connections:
/Base_R: Base Res.1, J2.1
/collecter: D2.2 (A), LED.1 (K), Q1 (BC547).1 (C), Relay.1
GND: J1.2, J2.2, Q1 (BC547).3 (E)
unnamed: LED.2 (A), R2.2
unnamed: J3.1, Relay.4
unnamed: J3.2, Relay.3
unnamed: J3.3, Relay.5
unnamed: Base Res.2, Q1 (BC547).2 (B)
VCC: D2.1 (K), J1.1, R2.1, Relay.2

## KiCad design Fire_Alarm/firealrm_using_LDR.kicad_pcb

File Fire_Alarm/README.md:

# 🔥 Fire Alarm System — PCB Project (As part of my Semester-II curriculum)
   A simple and low-cost fire alarm system based on LDR (Light Dependent Resistor) and BJT. This project includes the schematic and PCB layout designed in KiCad.

---

## ⚙ Working Principle
  * The system uses an LDR (Light Dependent Resistor) to detect changes in light intensity.
  * In the event of a fire, the light from flames increases the light falling on the LDR, reducing its resistance.
  * This change triggers a BJT (Bipolar Junction Transistor) to conduct, activating the buzzer and LED to alert nearby individuals.

---

## 📌 Objective
   To design, simulate, and layout a compact fire detection circuit that responds to light intensity variations, suitable for fire-prone zones or domestic safety applications.

---

## ⚙ Components Used
| No. | Components           | Specifications          |
| :---: | :--------------------: | :-----------------------: |
| 1.  | Battery              | 9V                      |
| 2.  | Transistor (NPN BJT) | BC547                   |
| 3.  | LDR                  | Standard                |
| 4.  | Resistors            |                         |
| 5.  | LED                  | Red (2V forward drop)   |
| 6.  | Buzzer               | 5V-9V piezo or magnetic |

---

## 📷 Preview

### 🖼 Schematic Circuit Diagram  

### 📐 PCB Layout  

### 🧊 3-D Front View  

---

## 🔄 Future Improvements
- Add temperature, smoke and IR sensors 
- Microcontroller integration (e.g. ATmega328 or ESP32)
- IoT capability for remote alerts (e.g., SMS / Blynk app)
- Adjustable Sensitivity

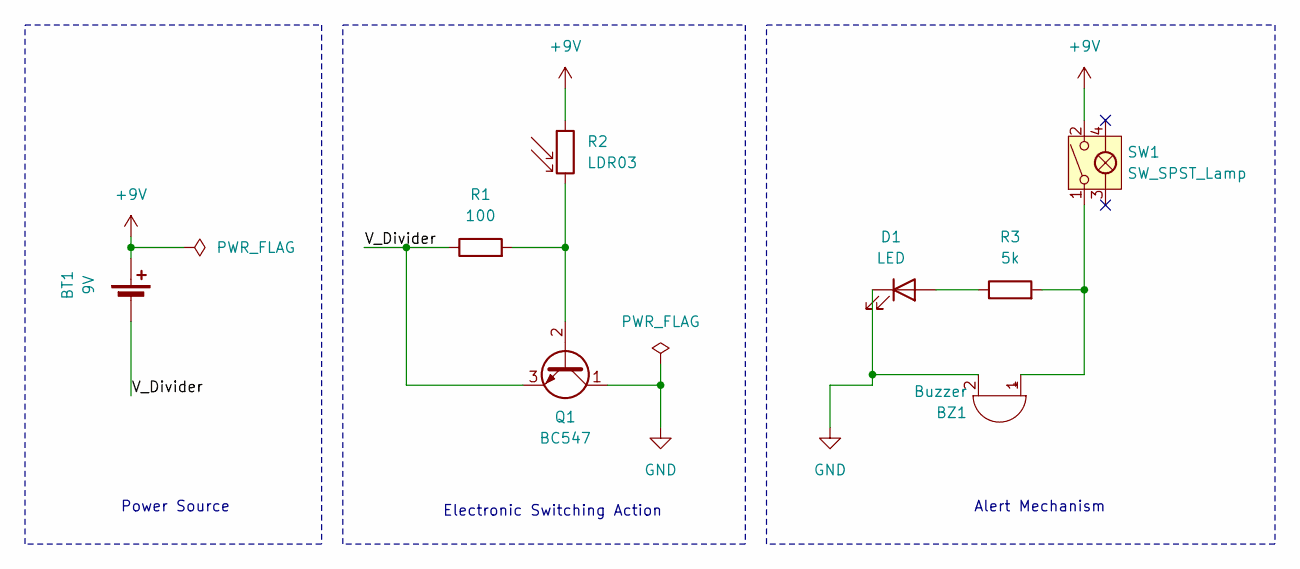
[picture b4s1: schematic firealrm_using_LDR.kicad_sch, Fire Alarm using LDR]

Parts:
BT1: 9V; TerminalBlock_Phoenix_MPT-0,5-2-2.54_1x02_P2.54mm_Horizontal
BZ1: Buzzer; Buzzer_12x9.5RM7.6
D1: LED; LED_D5.0mm
Q1: BC547; TO-92_Inline
R1: 100; R_Axial_DIN0207_L6.3mm_D2.5mm_P7.62mm_Horizontal
R2: LDR03; R_LDR_10x8.5mm_P7.6mm_Vertical
R3: 5k; R_Axial_DIN0207_L6.3mm_D2.5mm_P7.62mm_Horizontal
SW1: SW_SPST_Lamp; SW_DIP_SPSTx02_Piano_10.8x6.64mm_W7.62mm_P2.54mm

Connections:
+9V: BT1.1 (+), R2.1, SW1.2
/V_Divider: BT1.2 (-), Q1.3 (E), R1.1
GND: BZ1.2 (-), D1.1 (K), Q1.1 (C)
unnamed: BZ1.1 (+), R3.2, SW1.1
unnamed: D1.2 (A), R3.1
unnamed: Q1.2 (B), R1.2, R2.2

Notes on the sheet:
Electronic Switching Action
Power Source
Alert Mechanism

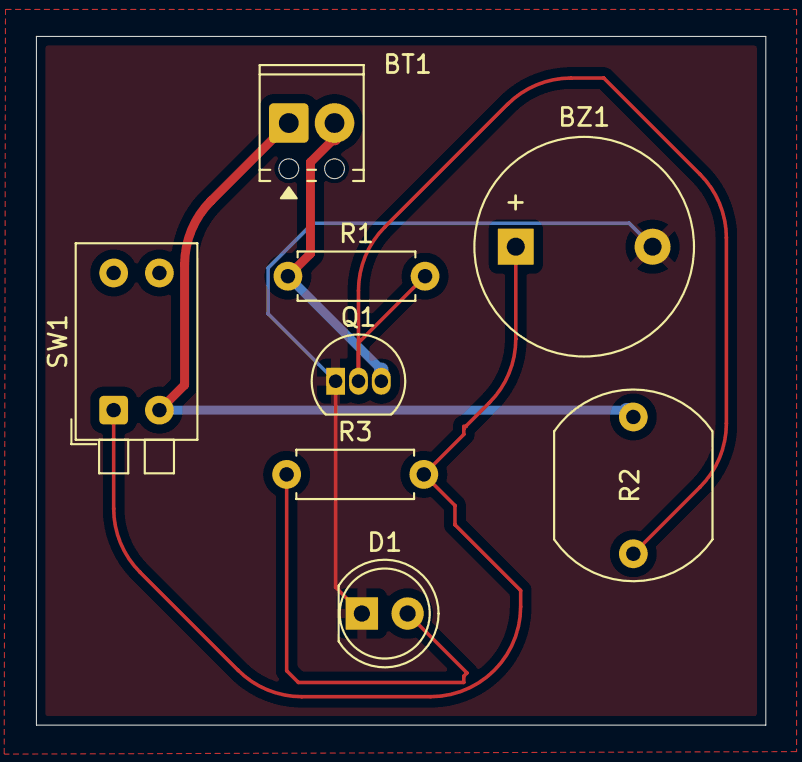
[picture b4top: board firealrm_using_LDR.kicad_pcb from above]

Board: 2 copper layers, 40.5 x 38.3 mm, 8 parts (0 on the bottom side), 6 nets.

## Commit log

2025-07-22 Initial commit: Simple Fire Alarm
2025-07-22 Added schematic images
2025-08-02 Added Relay Driver schematic files
2025-08-02 Renamed kiCAD project files
2025-08-02 Added README for Relay Driver PCB
2025-08-02 Added README
2025-08-02 Modified README
2025-08-02 Modified README file
2025-08-02 Added README file
2025-08-02 Updated root README.md
2025-08-03 Added PCB file
2025-08-03 Schematic added
2025-08-03 PCB screenshot added
2025-08-03 3D img added
2025-08-03 Fire Alarm folder name renamed
2026-04-09 Removed ignored folders from tracking
2026-04-09 README updated
2026-04-09 Schematic Completed
2026-04-11 Footprints assigned
2026-04-11 README edited
2026-04-11 Schematic reaaranged, Board setup loaded
2026-04-13 LF PCB added in the README
2026-04-13 LF PCB quoted in the README
2026-04-13 ESP32 Smart Plug Repo added in README
2026-04-14 Schematic aligned
2026-04-14 PCB layout started
2026-04-14 Project Name changed
2026-04-15 Charging moduke and buck converter added
2026-04-15 Sensor Architecture improvised in the Schematics
2026-04-17 PCB Layout done
2026-04-17 Removed history files and updated PCB layout
2026-04-29 PCB Layout modified
2026-04-29 DRC Errors resolved
2026-04-29 Battery footprint changed
2026-04-29 Routing strted
2026-05-04 PCB Routing done
2026-05-04 Schematics plotted
2026-05-04 .gitignore files added
2026-05-04 .gitignore file added
2026-05-04 .gitignore added
2026-05-04 Stitching vias added
2026-05-04 README added
2026-05-04 Folders renamed
2026-05-04 File name renamed
2026-05-06 File named changed
2026-05-06 Description altered
2026-06-11 Schematic v1.0 done
2026-06-11 Folder organisation updated
2026-06-11 ERC done!
2026-06-12 Schematic updated
2026-06-12 README file added
2026-06-12 Schematic Img added
2026-06-13 Footprint assigned
